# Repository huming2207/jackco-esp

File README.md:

# JackcoESP development boards

## JackcoESP32-PICO

See `jackco-esp32-pico` directory for more details

### Major components

- SoC/Module: ESP32-PICO-D4
- RAM: 520KB built-in SRAM, with ESP pSRAM pads for optional pSRAM 
- Antenna: Rainsun AN9520

## License

CC-BY-NC-SA 4.0

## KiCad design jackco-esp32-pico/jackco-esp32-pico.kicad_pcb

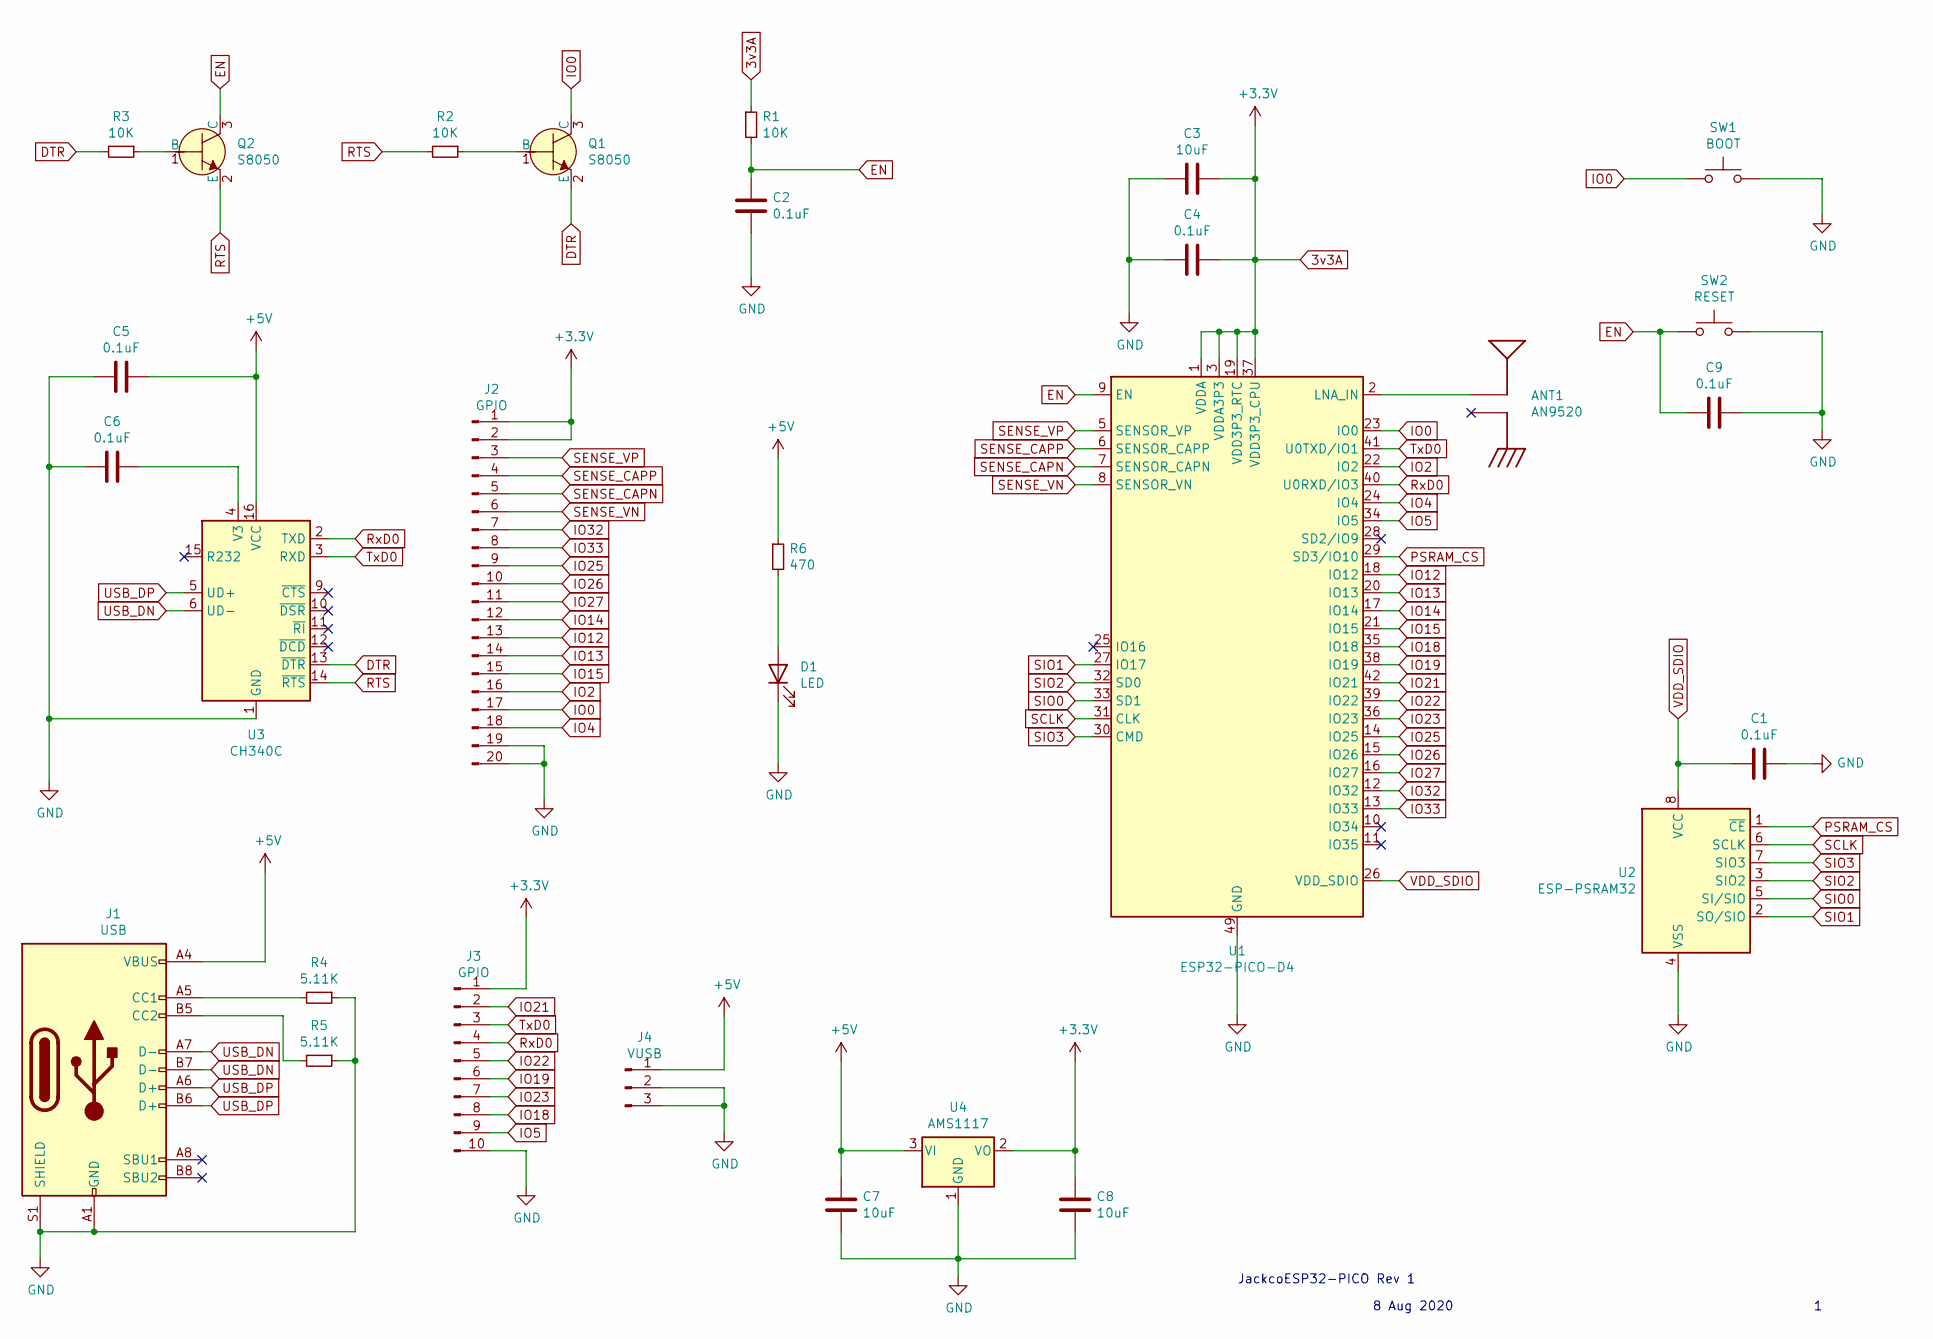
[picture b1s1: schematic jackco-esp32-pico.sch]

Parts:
ANT1: AN9520; SMD_ANT9520
C1, C2, C4, C5, C6, C9: 0.1uF; C_0603_1608Metric_Pad1.05x0.95mm_HandSolder
C3, C7, C8: 10uF; C_0805_2012Metric_Pad1.15x1.40mm_HandSolder
D1: LED; LED_0805_2012Metric_Pad1.15x1.40mm_HandSolder
J1: USB; USB_C_Receptacle_HRO_TYPE-C-31-M-12
J2: GPIO; PinHeader_1x20_P2.54mm_Vertical
J3: GPIO; PinHeader_1x10_P2.54mm_Vertical
J4: VUSB; PinSocket_1x03_P2.54mm_Vertical
Q1, Q2: S8050; SOT-23
R1, R2, R3: 10K; R_0603_1608Metric_Pad1.05x0.95mm_HandSolder
R4, R5: 5.11K; R_0603_1608Metric_Pad1.05x0.95mm_HandSolder
R6: 470; R_0603_1608Metric_Pad1.05x0.95mm_HandSolder
SW1: BOOT; SW_SPST_REED_CT05-XXXX-J1
SW2: RESET; SW_SPST_REED_CT05-XXXX-J1
U1: ESP32-PICO-D4; QFN-48-1EP_7x7mm_P0.5mm_EP5.3x5.3mm
U2: ESP-PSRAM32; SOIC-8_3.9x4.9mm_P1.27mm
U3: CH340C; SOIC-16_3.9x9.9mm_P1.27mm
U4: AMS1117; SOT-223-3_TabPin2

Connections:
3v3A: C3.1, C4.2, C8.1, J2.1, J2.2, J3.1, R1.1, U1.1 (VDDA), U1.3 (VDDA3P3), U1.4 (VDDA3P3), U1.19 (VDD3P3_RTC), U1.37 (VDD3P3_CPU), U1.43 (VDDA), U1.46 (VDDA), U4.2 (VO)
+5V: C5.1, C7.1, J1.A4 (VBUS), J1.A9 (VBUS), J1.B4 (VBUS), J1.B9 (VBUS), J4.1, R6.1, U3.16 (VCC), U4.3 (VI)
DTR: Q1.2 (E), R3.2, U3.13 (~DTR)
EN: C2.1, C9.2, Q2.3 (C), R1.2, SW2.1, U1.9 (EN)
GND: C1.1, C2.2, C3.2, C4.1, C5.2, C6.2, C7.2, C8.2, C9.1, D1.1 (K), J1.A1 (GND), J1.A12 (GND), J1.B1 (GND), J1.B12 (GND), J1.S1 (SHIELD), J2.19, J2.20, J3.10, J4.2, J4.3, R4.1, R5.1, SW1.2, SW2.2, U1.49 (GND), U2.4 (VSS), U3.1 (GND), U4.1 (GND)
IO0: J2.17, Q1.3 (C), SW1.1, U1.23 (IO0)
IO2: J2.16, U1.22 (IO2)
IO4: J2.18, U1.24 (IO4)
IO5: J3.9, U1.34 (IO5)
IO12: J2.13, U1.18 (IO12)
IO13: J2.14, U1.20 (IO13)
IO14: J2.12, U1.17 (IO14)
IO15: J2.15, U1.21 (IO15)
IO18: J3.8, U1.35 (IO18)
IO19: J3.6, U1.38 (IO19)
IO21: J3.2, U1.42 (IO21)
IO22: J3.5, U1.39 (IO22)
IO23: J3.7, U1.36 (IO23)
IO25: J2.9, U1.14 (IO25)
IO26: J2.10, U1.15 (IO26)
IO27: J2.11, U1.16 (IO27)
IO32: J2.7, U1.12 (IO32)
IO33: J2.8, U1.13 (IO33)
unnamed: ANT1.P$FEED, U1.2 (LNA_IN)
unnamed: C6.1, U3.4 (V3)
unnamed: D1.2 (A), R6.2
unnamed: J1.A5 (CC1), R4.2
unnamed: J1.B5 (CC2), R5.2
unnamed: Q1.1 (B), R2.1
unnamed: Q2.1 (B), R3.1
PSRAM_CS: U1.29 (SD3/IO10), U2.1 (~CE)
RTS: Q2.2 (E), R2.2, U3.14 (~RTS)
RxD0: J3.4, U1.40 (U0RXD/IO3), U3.2 (TXD)
SCLK: U1.31 (CLK), U2.6 (SCLK)
SENSE_CAPN: J2.5, U1.7 (SENSOR_CAPN)
SENSE_CAPP: J2.4, U1.6 (SENSOR_CAPP)
SENSE_VN: J2.6, U1.8 (SENSOR_VN)
SENSE_VP: J2.3, U1.5 (SENSOR_VP)
SIO0: U1.33 (SD1), U2.5 (SI/SIO)
SIO1: U1.27 (IO17), U2.2 (SO/SIO)
SIO2: U1.32 (SD0), U2.3 (SIO2)
SIO3: U1.30 (CMD), U2.7 (SIO3)
TxD0: J3.3, U1.41 (U0TXD/IO1), U3.3 (RXD)
USB_DN: J1.A7 (D-), J1.B7 (D-), U3.6 (UD-)
USB_DP: J1.A6 (D+), J1.B6 (D+), U3.5 (UD+)
VDD_SDIO: C1.2, U1.26 (VDD_SDIO), U2.8 (VCC)

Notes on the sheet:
JackcoESP32-PICO Rev 1
8 Aug 2020

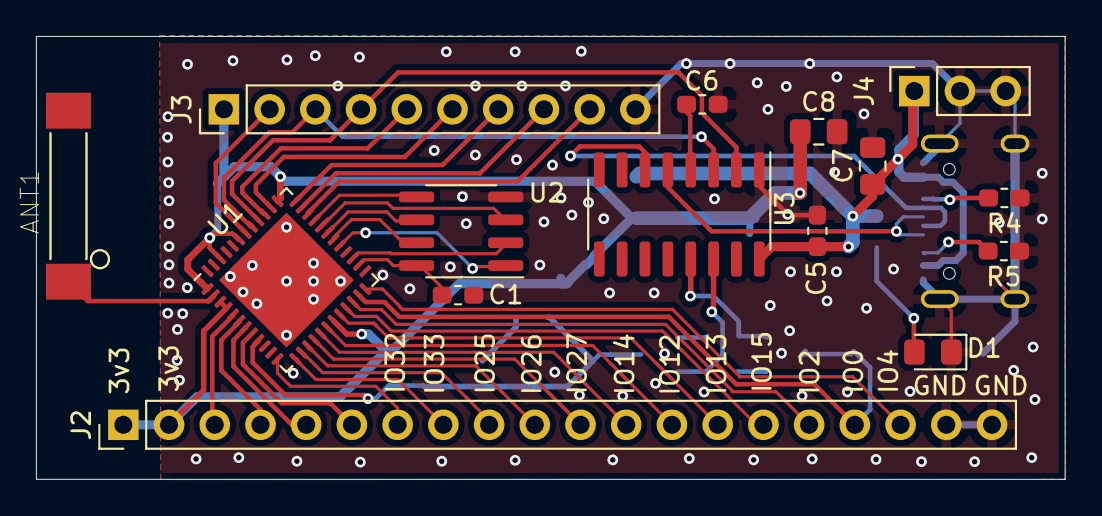
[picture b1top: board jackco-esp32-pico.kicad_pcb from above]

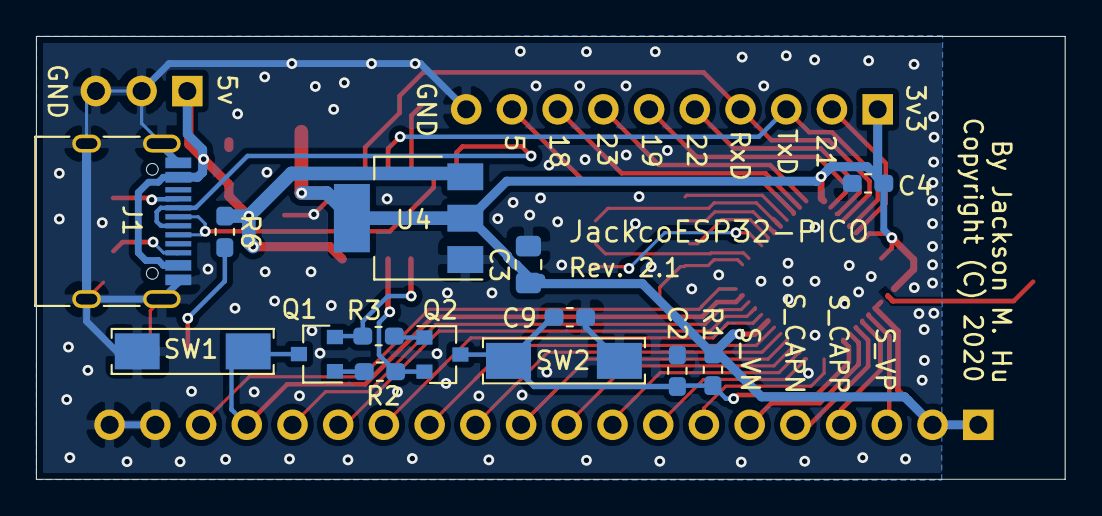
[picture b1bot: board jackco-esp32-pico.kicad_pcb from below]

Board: 2 copper layers, 57.2 x 24.6 mm, 29 parts (14 on the bottom side), 46 nets.

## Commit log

2020-08-07 Add reset/reboot buttons
2020-08-08 Add PCB Rev 1
2020-08-09 Update gerber
2020-08-09 Add 99x99mm, 4x1 panel
2020-08-09 Add PDFs, rename project
2020-08-09 Add README
2020-08-21 Move panelized board Vcut to outline layer
2020-11-11 Redesign 5v domain, fix wrong S8050
2020-11-11 Drop all panels
2020-11-11 Add Rev 2's panel
2020-11-13 Final adjustments for Rev 2.1
2020-11-13 Generate gerber for Rev 2.1
2020-11-13 Add Rev 2.1's schematic

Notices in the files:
jackco-esp32-pico/jackco-esp32-pico.kicad_pcb:
Copyright (C) 2020
